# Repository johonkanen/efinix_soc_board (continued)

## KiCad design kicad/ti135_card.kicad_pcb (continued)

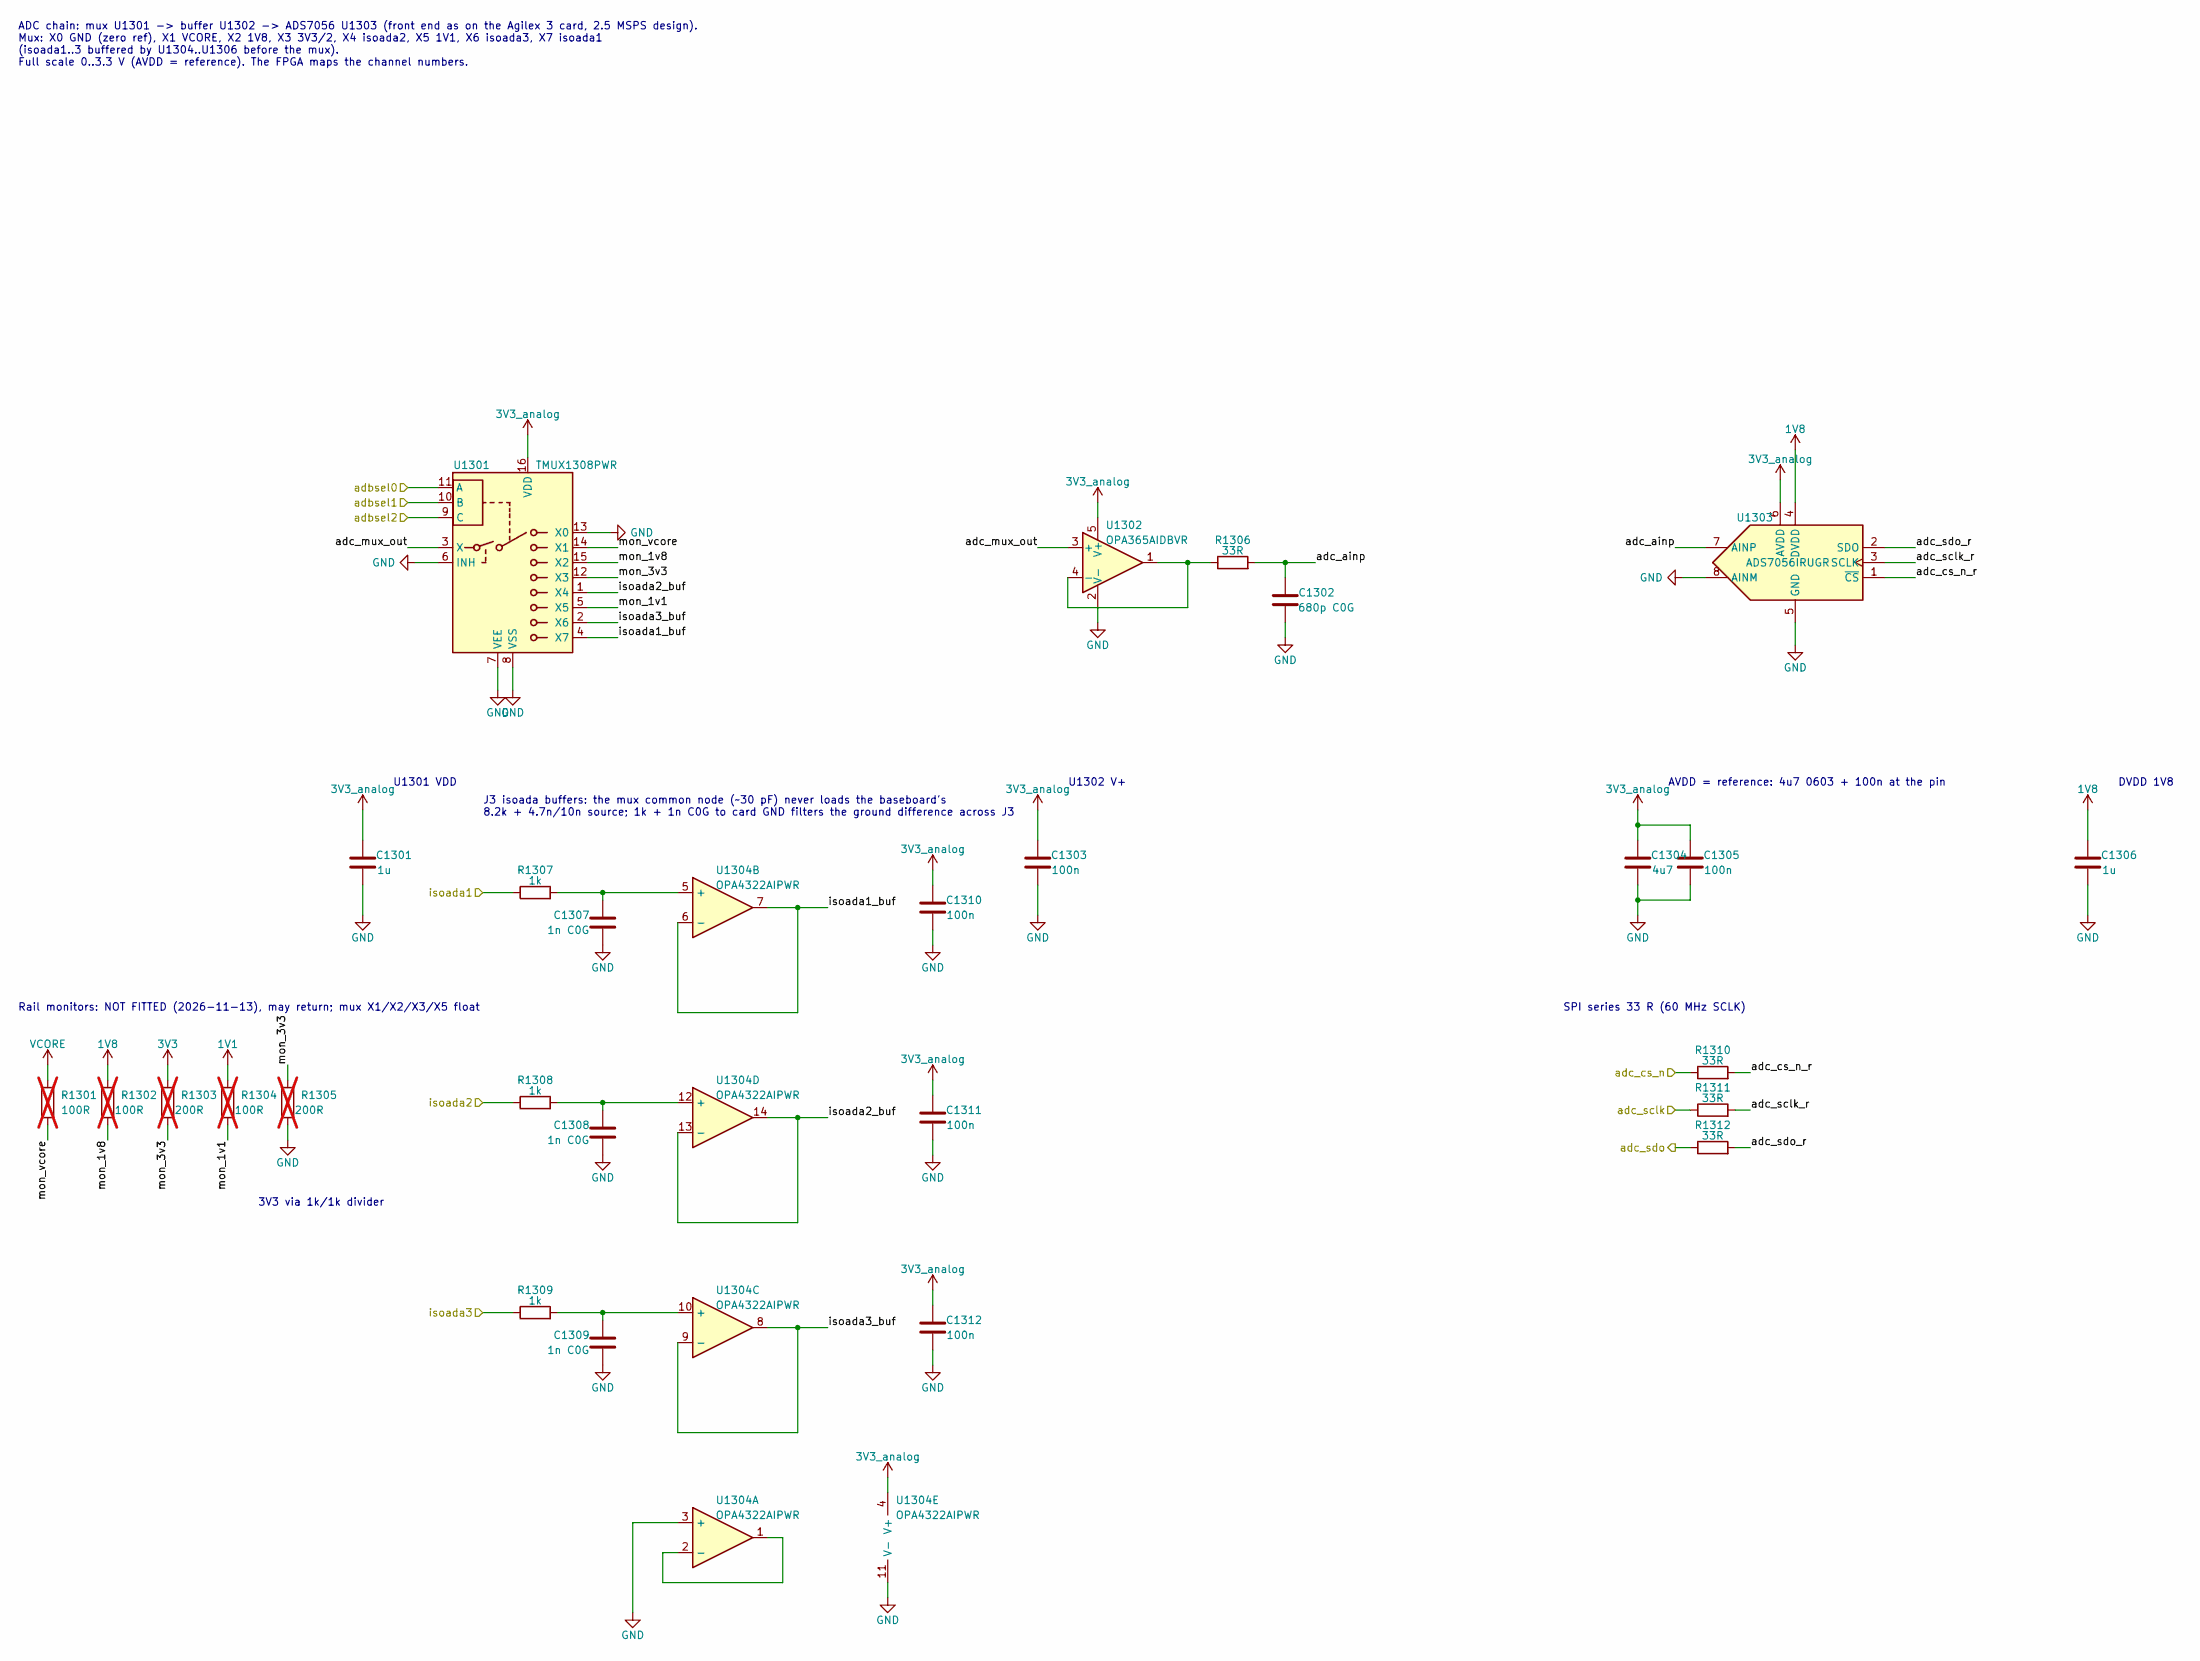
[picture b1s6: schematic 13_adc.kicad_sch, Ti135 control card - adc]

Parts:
C1301: 1u; C_0402_1005Metric; LCSC C52923
C1302: 680p C0G; C_0402_1005Metric; LCSC C126514
C1303, C1305, C1310, C1311, C1312: 100n; C_0402_1005Metric; LCSC C1525
C1304: 4u7; C_0603_1608Metric; LCSC C19666
C1306: 1u; C_0201_0603Metric; LCSC C272877
C1307, C1308, C1309: 1n C0G; C_0402_1005Metric; LCSC C76947
R1301, R1302, R1304: 100R; R_0402_1005Metric; LCSC C25076; not fitted
R1303, R1305: 200R; R_0402_1005Metric; LCSC C25087; not fitted
R1306, R1310, R1311, R1312: 33R; R_0402_1005Metric; LCSC C25105
R1307, R1308, R1309: 1k; R_0402_1005Metric; LCSC C11702
U1301: TMUX1308PWR; TSSOP-16_4.4x5mm_P0.65mm; LCSC C970231
U1302: OPA365AIDBVR; SOT-23-5; LCSC C96626
U1303: ADS7056IRUGR; ads7056; LCSC C2669798
U1304: OPA4322AIPWR; TSSOP-14_4.4x5mm_P0.65mm; LCSC C486027

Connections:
1V8: C1306.1, R1302.1, U1303.4 (DVDD); also elsewhere on the board
3V3_analog: C1301.1, C1303.1, C1304.1, C1305.1, C1310.1, C1311.1, C1312.1, U1301.16 (VDD), U1302.5 (V+), U1303.6 (AVDD), U1304.4 (V+); also elsewhere on the board
/13 adc/adc_ainp: C1302.1, R1306.2, U1303.7 (AINP)
/13 adc/adc_cs_n_r: R1310.2, U1303.1 (~CS)
/13 adc/adc_mux_out: U1301.3 (X), U1302.3 (+)
/13 adc/adc_sclk_r: R1311.2, U1303.3 (SCLK)
/13 adc/adc_sdo_r: R1312.2, U1303.2 (SDO)
/13 adc/isoada1_buf: U1301.4 (X7), U1304.6 (-), U1304.7
/13 adc/isoada2_buf: U1301.1 (X4), U1304.13 (-), U1304.14
/13 adc/isoada3_buf: U1301.2 (X6), U1304.8, U1304.9 (-)
/13 adc/mon_1v1: R1304.2, U1301.5 (X5)
/13 adc/mon_1v8: R1302.2, U1301.15 (X2)
/13 adc/mon_3v3: R1303.2, R1305.1, U1301.12 (X3)
/13 adc/mon_vcore: R1301.2, U1301.14 (X1)
/adbsel0: U1301.11 (A); also elsewhere on the board
/adbsel1: U1301.10 (B); also elsewhere on the board
/adbsel2: U1301.9 (C); also elsewhere on the board
/adc_cs_n: R1310.1; also elsewhere on the board
/adc_sclk: R1311.1; also elsewhere on the board
/adc_sdo: R1312.1; also elsewhere on the board
/isoada1: R1307.1; also elsewhere on the board
/isoada2: R1308.1; also elsewhere on the board
/isoada3: R1309.1; also elsewhere on the board
GND: C1301.2, C1302.2, C1303.2, C1304.2, C1305.2, C1306.2, C1307.2, C1308.2, C1309.2, C1310.2, C1311.2, C1312.2, R1305.2, U1301.6 (INH), U1301.7 (VEE), U1301.8 (VSS), U1301.13 (X0), U1302.2 (V-), U1303.5 (GND), U1303.8 (AINM), U1304.3 (+), U1304.11 (V-); also elsewhere on the board
unnamed: R1306.1, U1302.1, U1302.4 (-)
unnamed: U1304.1, U1304.2 (-)
unnamed: C1307.1, R1307.2, U1304.5 (+)
unnamed: C1309.1, R1309.2, U1304.10 (+)
unnamed: C1308.1, R1308.2, U1304.12 (+)

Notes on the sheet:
Rail monitors: NOT FITTED (2026-11-13), may return; mux X1/X2/X3/X5 float
U1301 VDD
DVDD 1V8
SPI series 33 R (60 MHz SCLK)
U1302 V+
3V3 via 1k/1k divider
ADC chain: mux U1301 -> buffer U1302 -> ADS7056 U1303 (front end as on the Agilex 3 card, 2.5 MSPS design). Mux: X0 GND (zero ref), X1 VCORE, X2 1V8, X3 3V3/2, X4 isoada2, X5 1V1, X6 isoada3, X7 isoada1 (isoada1..3 buffered by U1304..U1306 before the mux). Full scale 0..3.3 V (AVDD = reference). Th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
J3 isoada buffers: the mux common node (~30 pF) never loads the baseboard's 8.2k + 4.7n/10n source; 1k + 1n C0G to card GND filters the ground difference across J3
AVDD = reference: 4u7 0603 + 100n at the pin

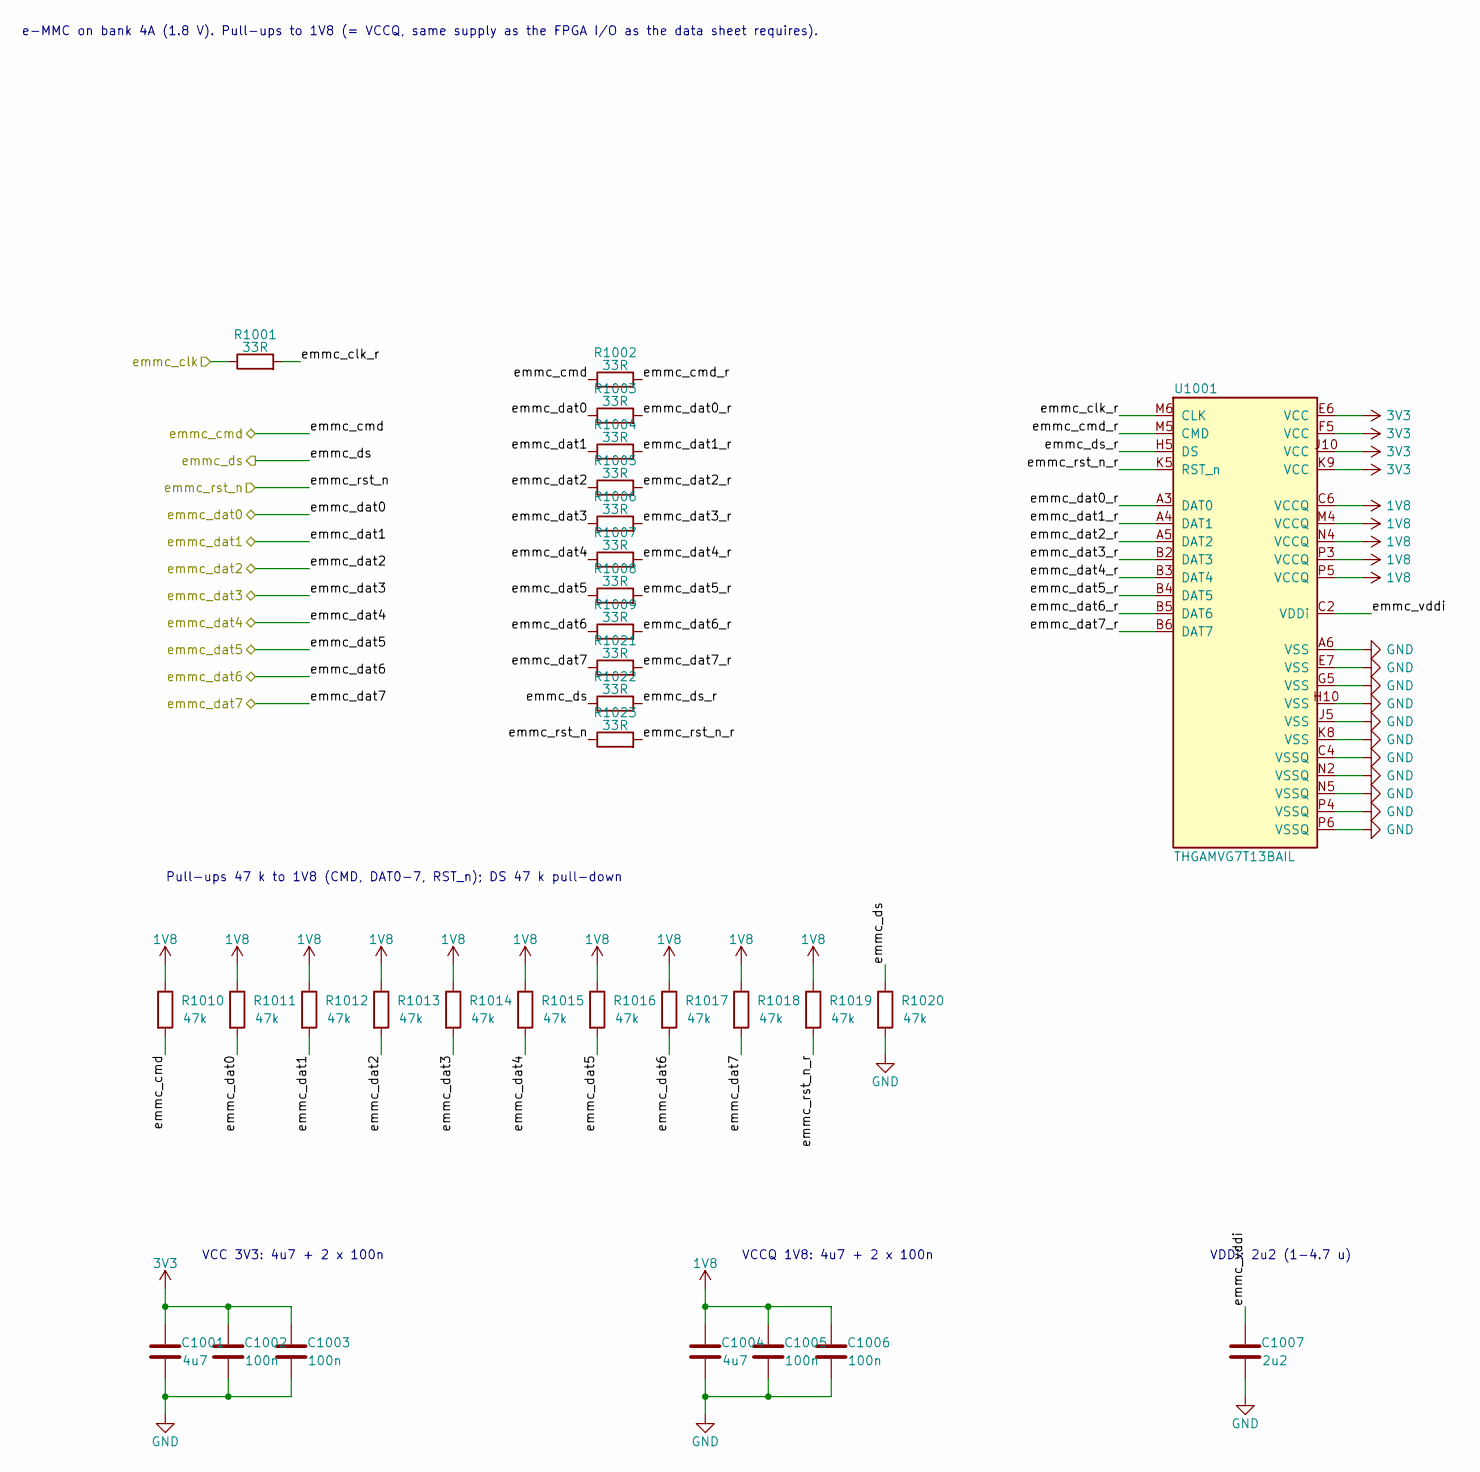
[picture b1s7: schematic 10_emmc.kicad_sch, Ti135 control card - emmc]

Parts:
C1001, C1004: 4u7; C_0201_0603Metric; LCSC C5969171
C1002, C1003, C1005, C1006: 100n; C_0201_0603Metric; LCSC C190183
C1007: 2u2; C_0201_0603Metric; LCSC C77762
R1001, R1002, R1003, R1004, R1005, R1006, R1007, R1008, R1009, R1021, R1022, R1023: 33R; R_0201_0603Metric; LCSC C320843
R1010, R1011, R1012, R1013, R1014, R1015, R1016, R1017, R1018, R1019, R1020: 47k; R_0201_0603Metric; LCSC C270345
U1001: THGAMVG7T13BAIL; LFBGA-153_11.5x13mm_Layout14x14_P0.5mm; LCSC C7599693

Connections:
1V8: C1004.1, C1005.1, C1006.1, R1010.1, R1011.1, R1012.1, R1013.1, R1014.1, R1015.1, R1016.1, R1017.1, R1018.1, R1019.1, U1001.C6 (VCCQ), U1001.M4 (VCCQ), U1001.N4 (VCCQ), U1001.P3 (VCCQ), U1001.P5 (VCCQ); also elsewhere on the board
3V3: C1001.1, C1002.1, C1003.1, U1001.E6 (VCC), U1001.F5 (VCC), U1001.J10 (VCC), U1001.K9 (VCC); also elsewhere on the board
/10 emmc/emmc_clk_r: R1001.2, U1001.M6 (CLK)
/10 emmc/emmc_cmd_r: R1002.2, U1001.M5 (CMD)
/10 emmc/emmc_dat0_r: R1003.2, U1001.A3 (DAT0)
/10 emmc/emmc_dat1_r: R1004.2, U1001.A4 (DAT1)
/10 emmc/emmc_dat2_r: R1005.2, U1001.A5 (DAT2)
/10 emmc/emmc_dat3_r: R1006.2, U1001.B2 (DAT3)
/10 emmc/emmc_dat4_r: R1007.2, U1001.B3 (DAT4)
/10 emmc/emmc_dat5_r: R1008.2, U1001.B4 (DAT5)
/10 emmc/emmc_dat6_r: R1009.2, U1001.B5 (DAT6)
/10 emmc/emmc_dat7_r: R1021.2, U1001.B6 (DAT7)
/10 emmc/emmc_ds_r: R1022.2, U1001.H5 (DS)
/10 emmc/emmc_rst_n_r: R1019.2, R1023.2, U1001.K5 (RST_n)
/10 emmc/emmc_vddi: C1007.1, U1001.C2 (VDDi)
/emmc_clk: R1001.1; also elsewhere on the board
/emmc_cmd: R1002.1, R1010.2; also elsewhere on the board
/emmc_dat0: R1003.1, R1011.2; also elsewhere on the board
/emmc_dat1: R1004.1, R1012.2; also elsewhere on the board
/emmc_dat2: R1005.1, R1013.2; also elsewhere on the board
/emmc_dat3: R1006.1, R1014.2; also elsewhere on the board
/emmc_dat4: R1007.1, R1015.2; also elsewhere on the board
/emmc_dat5: R1008.1, R1016.2; also elsewhere on the board
/emmc_dat6: R1009.1, R1017.2; also elsewhere on the board
/emmc_dat7: R1018.2, R1021.1; also elsewhere on the board
/emmc_ds: R1020.1, R1022.1; also elsewhere on the board
/emmc_rst_n: R1023.1; also elsewhere on the board
GND: C1001.2, C1002.2, C1003.2, C1004.2, C1005.2, C1006.2, C1007.2, R1020.2, U1001.A6 (VSS), U1001.C4 (VSSQ), U1001.E7 (VSS), U1001.G5 (VSS), U1001.H10 (VSS), U1001.J5 (VSS), U1001.K8 (VSS), U1001.N2 (VSSQ), U1001.N5 (VSSQ), U1001.P4 (VSSQ), U1001.P6 (VSSQ); also elsewhere on the board

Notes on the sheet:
VCCQ 1V8: 4u7 + 2 x 100n
Pull-ups 47 k to 1V8 (CMD, DAT0-7, RST_n); DS 47 k pull-down
VCC 3V3: 4u7 + 2 x 100n
e-MMC on bank 4A (1.8 V). Pull-ups to 1V8 (= VCCQ, same supply as the FPGA I/O as the data sheet requires).
VDDi: 2u2 (1-4.7 u)

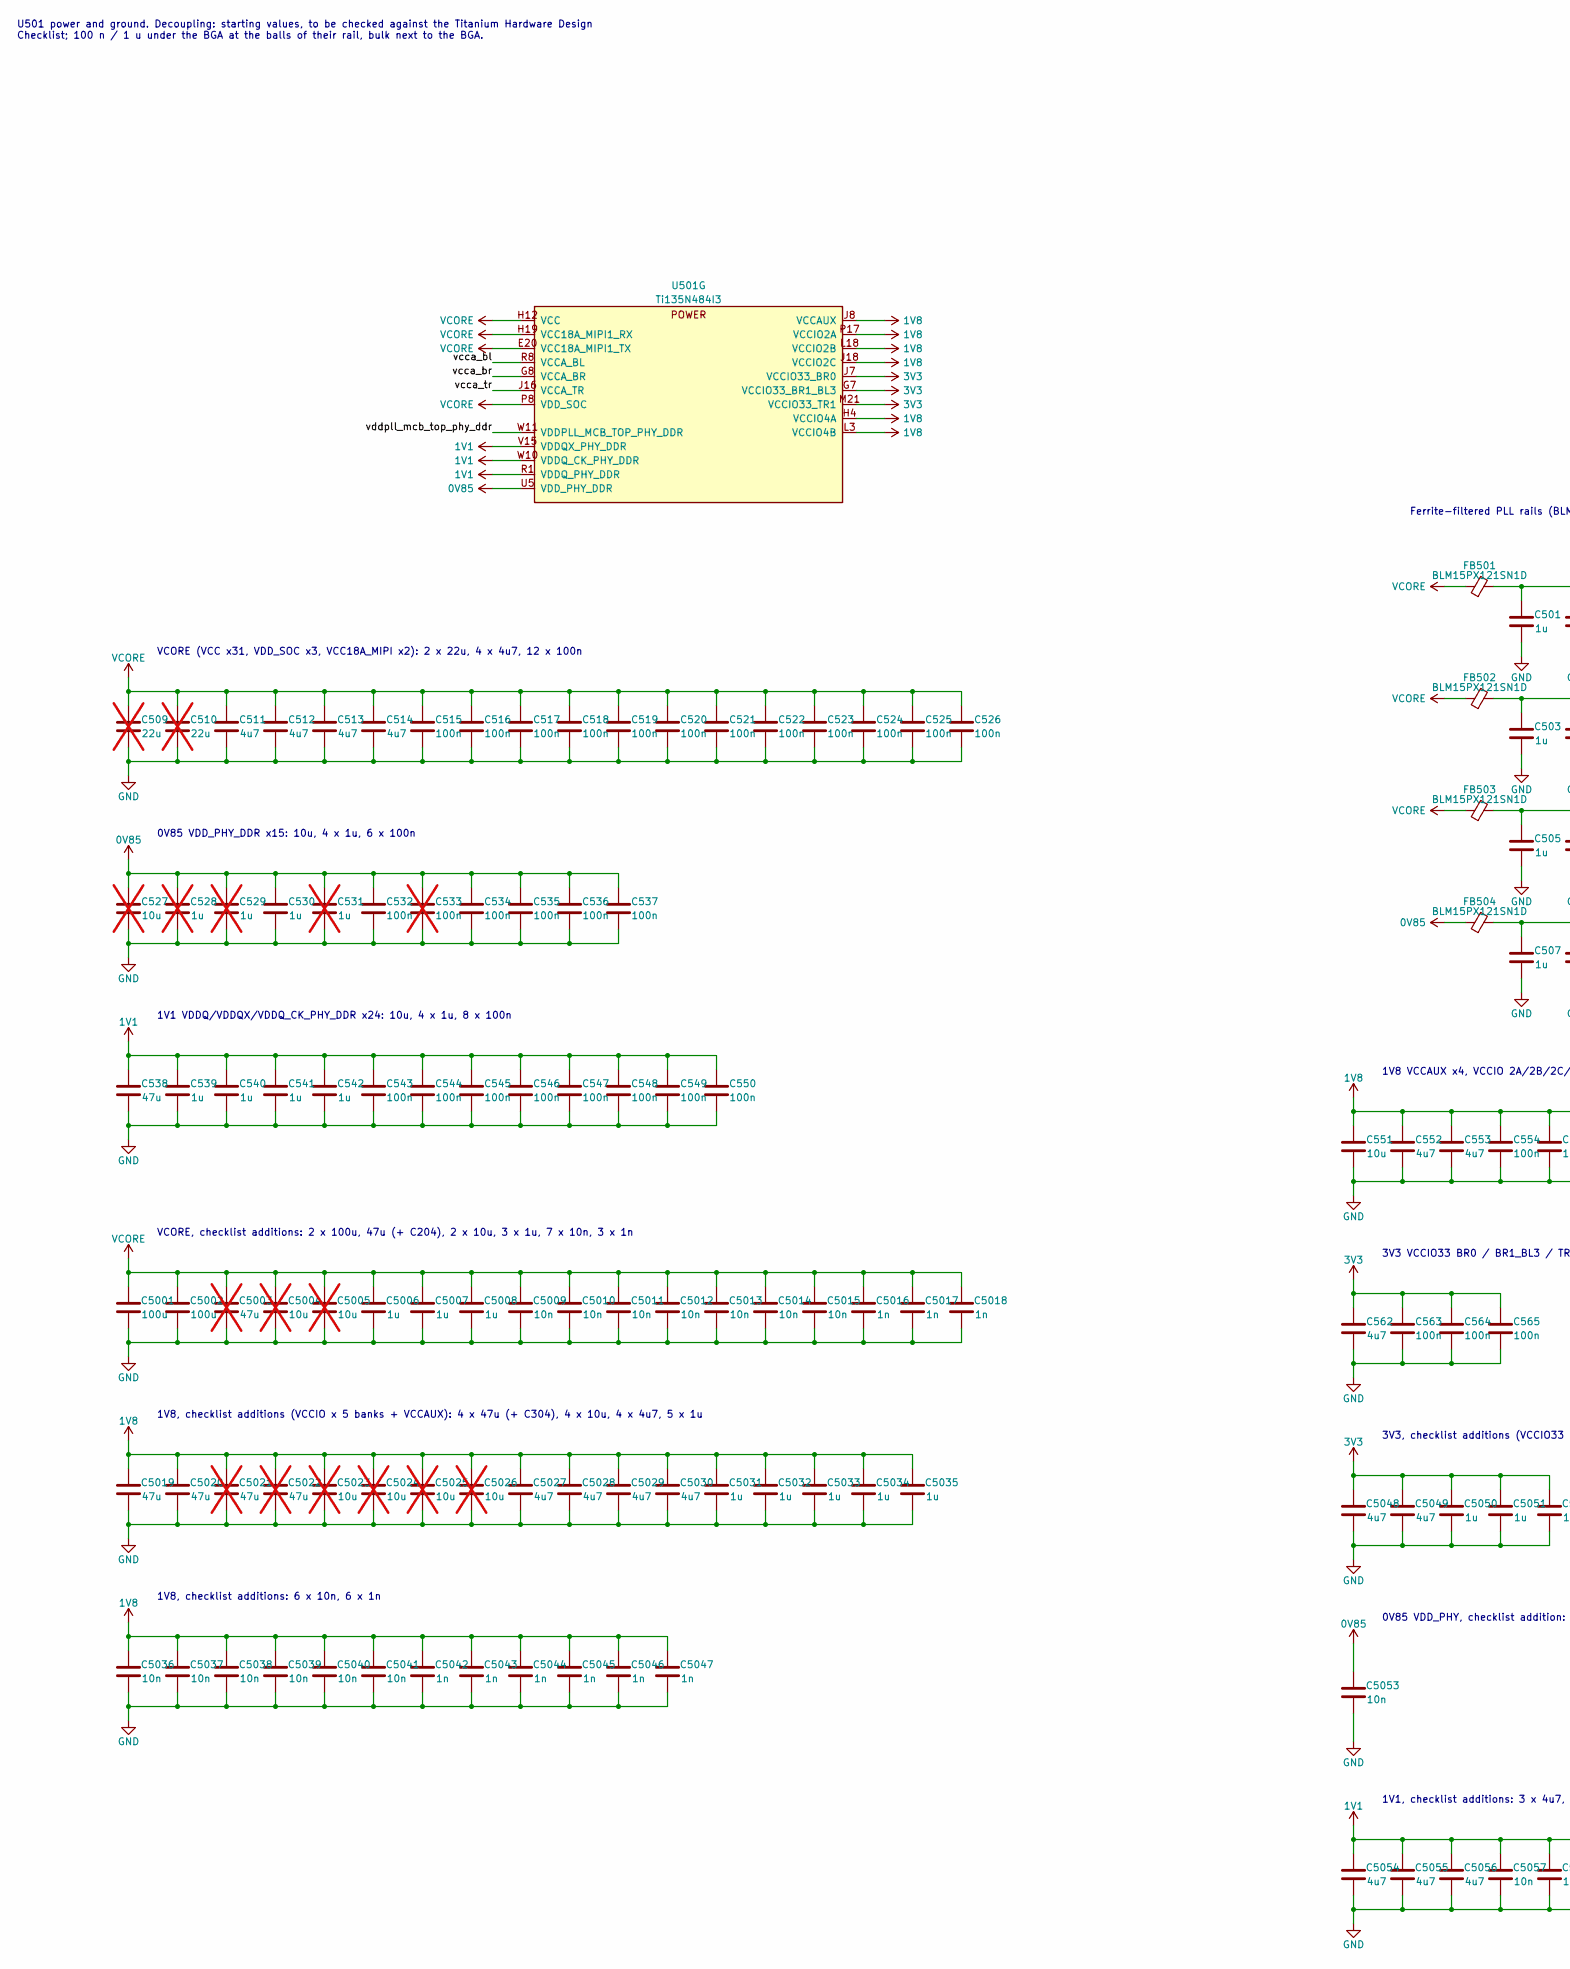
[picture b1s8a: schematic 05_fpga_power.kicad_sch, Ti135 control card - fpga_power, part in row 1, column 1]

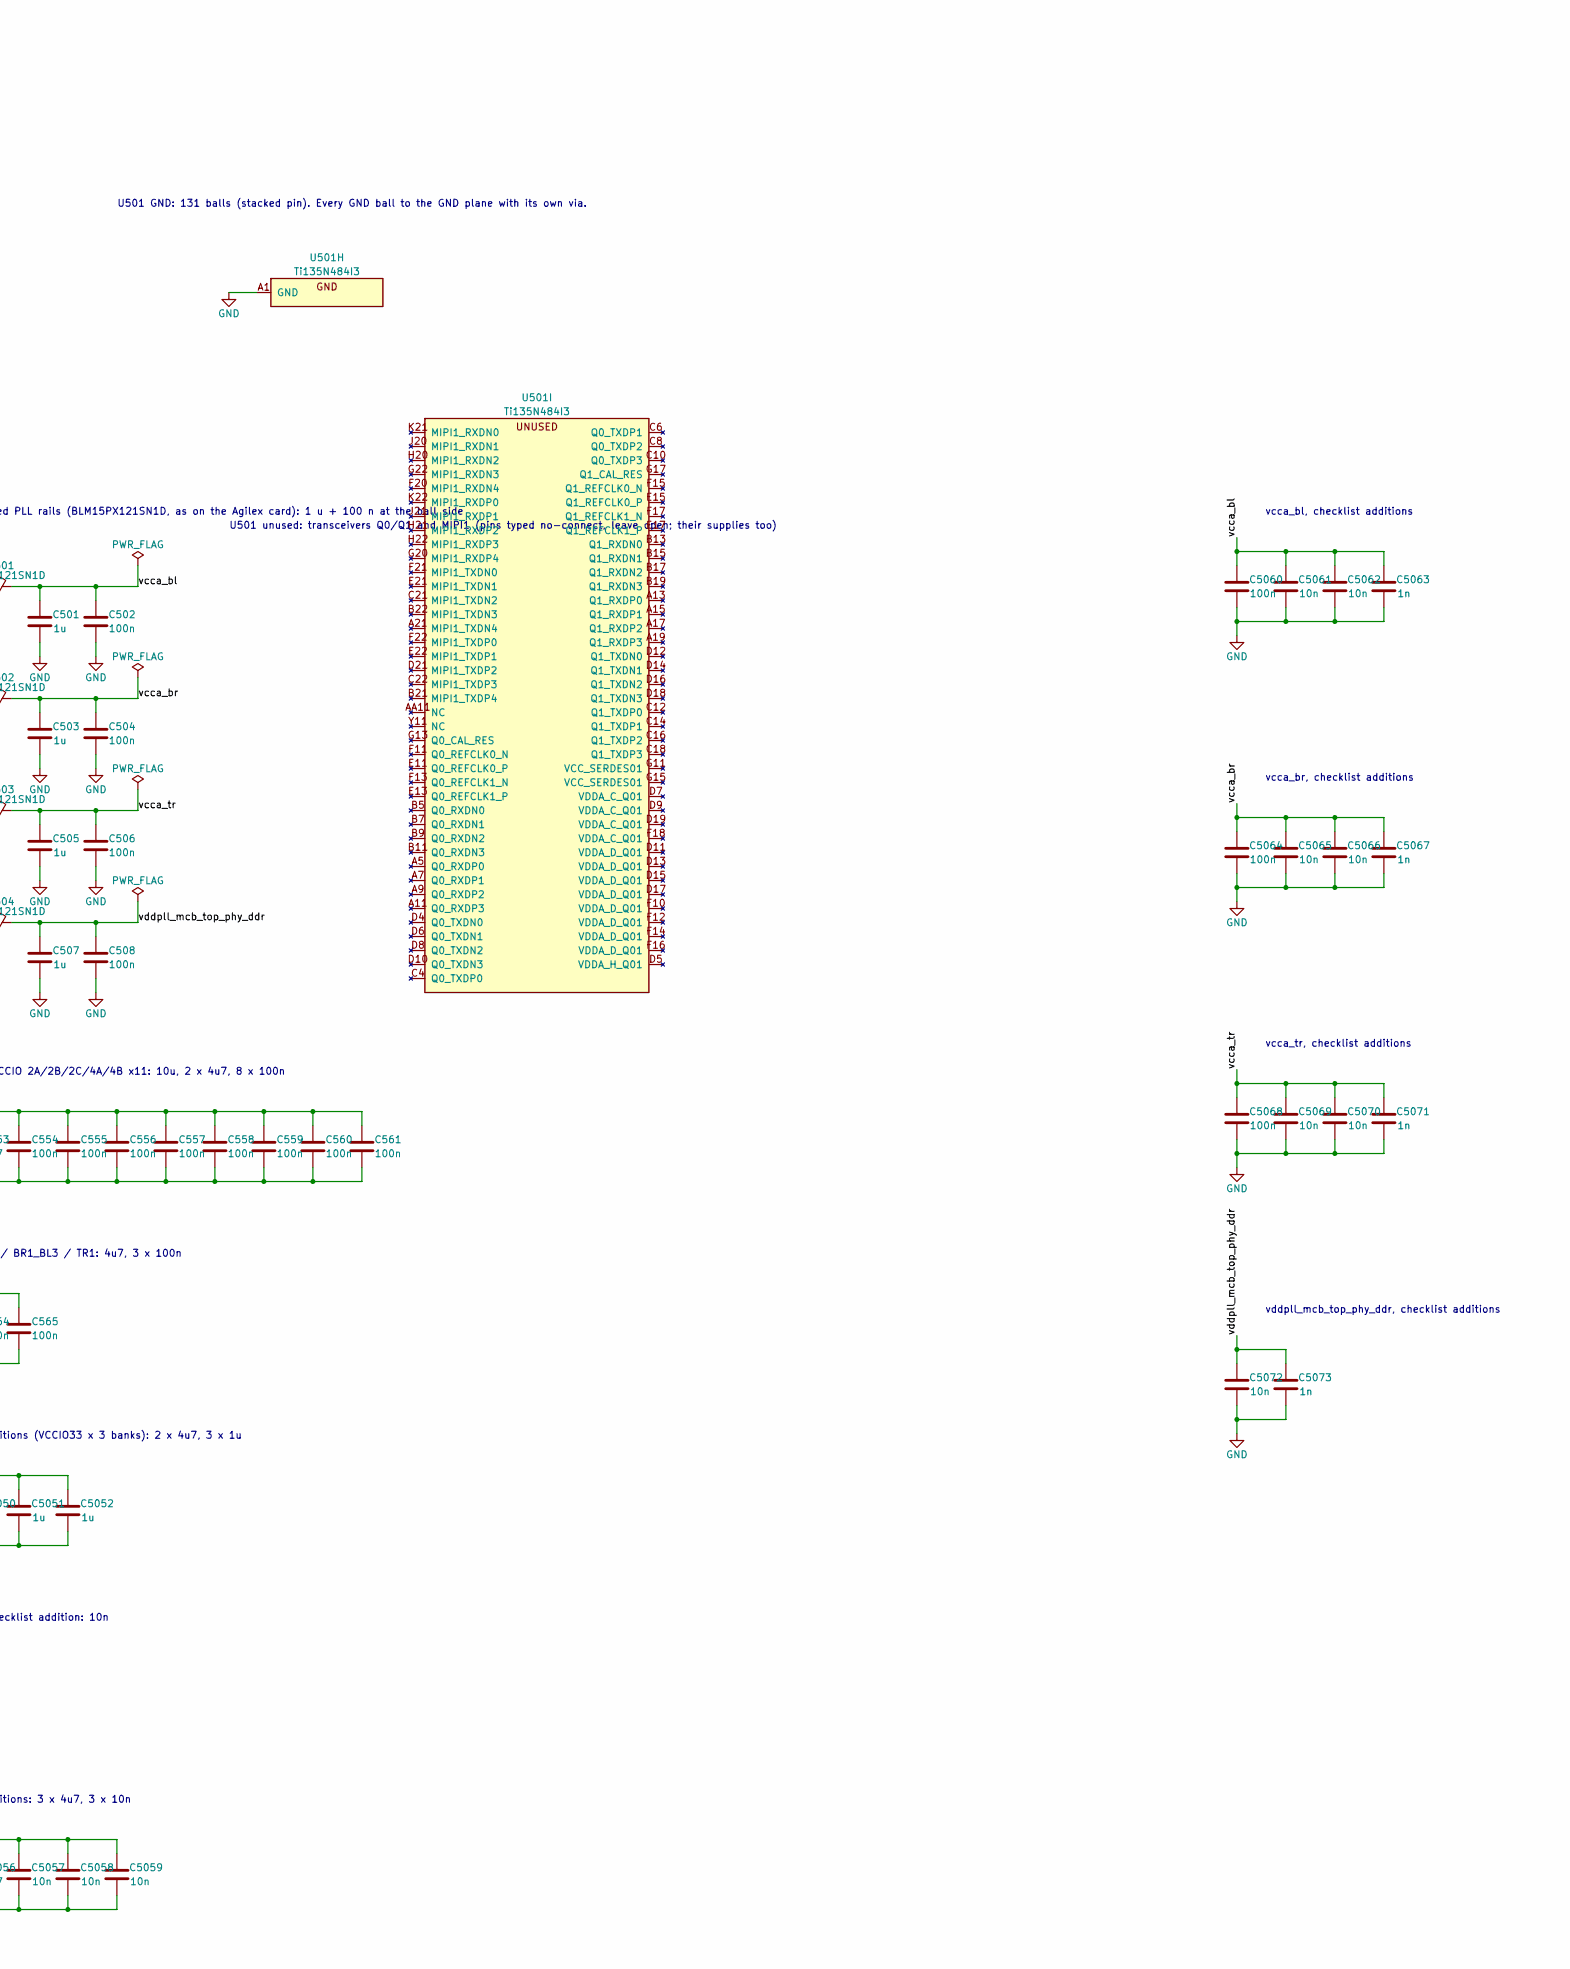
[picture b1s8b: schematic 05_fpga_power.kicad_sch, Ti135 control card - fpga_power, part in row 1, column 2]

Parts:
C501, C503, C505, C507, C5033: 1u; C_0402_1005Metric; LCSC C52923
C502, C504, C506, C508: 100n; C_0402_1005Metric; LCSC C1525
C509, C510: 22u; C_0805_2012Metric; LCSC C45783; not fitted
C511, C512, C513, C514, C552, C553, C5027, C5028, C5029, C5030, C5048, C5049, C5054, C5055, C5056: 4u7; C_0201_0603Metric; LCSC C47117441
C515, C516, C517, C518, C519, C520, C521, C522, C523, C524, C525, C526, C532, C534, C535, C536, C537, C543, C544, C545, C546, C547, C548, C549, C550, C554, C555, C556, C557, C558, C559, C560, C561, C563, C564, C565, C5060, C5064, C5068: 100n; C_0201_0603Metric; LCSC C190183
C527, C5004, C5005, C5023, C5024, C5025, C5026: 10u; C_0805_2012Metric; LCSC C15850; not fitted
C528, C529, C531: 1u; C_0201_0603Metric; LCSC C272877; not fitted
C530, C539, C540, C541, C542, C5006, C5007, C5008, C5031, C5032, C5034, C5035, C5050, C5051, C5052: 1u; C_0201_0603Metric; LCSC C272877
C533: 100n; C_0201_0603Metric; LCSC C190183; not fitted
C538, C5019, C5020: 47u; C_0805_2012Metric; LCSC C16780
C551: 10u; C_0805_2012Metric; LCSC C15850
C562: 4u7; C_0402_1005Metric; LCSC C23733
C5001, C5002: 100u; C_1206_3216Metric; LCSC C15008
C5003, C5021, C5022: 47u; C_0805_2012Metric; LCSC C16780; not fitted
C5009, C5010, C5011, C5012, C5013, C5014, C5015, C5036, C5037, C5038, C5039, C5040, C5041, C5053, C5057, C5058, C5059, C5061, C5062, C5065, C5066, C5069, C5070, C5072: 10n; C_0201_0603Metric; LCSC C76941
C5016, C5017, C5018, C5042, C5043, C5044, C5045, C5046, C5047, C5063, C5067, C5071, C5073: 1n; C_0201_0603Metric; LCSC C66942
FB501, FB502, FB503, FB504: BLM15PX121SN1D; L_0402_1005Metric; LCSC C88970
U501: Ti135N484I3; LFBGA-484_18x18mm_Layout22x22_P0.8mm

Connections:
0V85: C527.1, C528.1, C529.1, C530.1, C531.1, C532.1, C533.1, C534.1, C535.1, C536.1, C537.1, C5053.1, FB504.1, U501.U5 (VDD_PHY_DDR), U501.U6 (VDD_PHY_DDR), U501.U7 (VDD_PHY_DDR), U501.U8 (VDD_PHY_DDR), U501.U9 (VDD_PHY_DDR), U501.U10 (VDD_PHY_DDR), U501.U11 (VDD_PHY_DDR), U501.U12 (VDD_PHY_DDR), U501.U13 (VDD_PHY_DDR), U501.U14 (VDD_PHY_DDR), U501.U15 (VDD_PHY_DDR), U501.V7 (VDD_PHY_DDR), U501.V9 (VDD_PHY_DDR), U501.V11 (VDD_PHY_DDR), U501.V13 (VDD_PHY_DDR); also elsewhere on the board
1V1: C538.1, C539.1, C540.1, C541.1, C542.1, C543.1, C544.1, C545.1, C546.1, C547.1, C548.1, C549.1, C550.1, C5054.1, C5055.1, C5056.1, C5057.1, C5058.1, C5059.1, U501.AB3 (VDDQ_PHY_DDR), U501.R1 (VDDQ_PHY_DDR), U501.T2 (VDDQ_PHY_DDR), U501.T5 (VDDQ_PHY_DDR), U501.U18 (VDDQ_PHY_DDR), U501.U19 (VDDQ_PHY_DDR), U501.V1 (VDDQ_PHY_DDR), U501.V15 (VDDQX_PHY_DDR), U501.V20 (VDDQ_PHY_DDR), U501.V21 (VDDQ_PHY_DDR), U501.W6 (VDDQX_PHY_DDR), U501.W7 (VDDQX_PHY_DDR), U501.W8 (VDDQX_PHY_DDR), U501.W9 (VDDQX_PHY_DDR), U501.W10 (VDDQ_CK_PHY_DDR), U501.W12 (VDDQX_PHY_DDR), U501.W15 (VDDQX_PHY_DDR), U501.W17 (VDDQ_PHY_DDR), U501.Y3 (VDDQ_PHY_DDR), U501.Y6 (VDDQ_PHY_DDR), U501.Y8 (VDDQ_PHY_DDR), U501.Y10 (VDDQX_PHY_DDR), U501.Y12 (VDDQ_PHY_DDR), U501.Y22 (VDDQ_PHY_DDR); also elsewhere on the board
1V8: C551.1, C552.1, C553.1, C554.1, C555.1, C556.1, C557.1, C558.1, C559.1, C560.1, C561.1, C5019.1, C5020.1, C5021.1, C5022.1, C5023.1, C5024.1, C5025.1, C5026.1, C5027.1, C5028.1, C5029.1, C5030.1, C5031.1, C5032.1, C5033.1, C5034.1, C5035.1, C5036.1, C5037.1, C5038.1, C5039.1, C5040.1, C5041.1, C5042.1, C5043.1, C5044.1, C5045.1, C5046.1, C5047.1, U501.H4 (VCCIO4A), U501.J8 (VCCAUX), U501.J18 (VCCIO2C), U501.K5 (VCCIO4A), U501.L3 (VCCIO4B), U501.L18 (VCCIO2B), U501.M6 (VCCIO4A), U501.M16 (VCCAUX), U501.N4 (VCCIO4B), U501.N8 (VCCAUX), U501.N19 (VCCIO2B), U501.P2 (VCCIO4B), U501.P17 (VCCIO2A), U501.T4 (VCCIO4B), U501.U16 (VCCAUX); also elsewhere on the board
3V3: C562.1, C563.1, C564.1, C565.1, C5048.1, C5049.1, C5050.1, C5051.1, C5052.1, U501.G7 (VCCIO33_BR1_BL3), U501.J7 (VCCIO33_BR0), U501.M21 (VCCIO33_TR1); also elsewhere on the board
/05 fpga_power/vcca_bl: C501.1, C502.1, C5060.1, C5061.1, C5062.1, C5063.1, FB501.2, U501.R8 (VCCA_BL)
/05 fpga_power/vcca_br: C503.1, C504.1, C5064.1, C5065.1, C5066.1, C5067.1, FB502.2, U501.G8 (VCCA_BR)
/05 fpga_power/vcca_tr: C505.1, C506.1, C5068.1, C5069.1, C5070.1, C5071.1, FB503.2, U501.J16 (VCCA_TR)
/05 fpga_power/vddpll_mcb_top_phy_ddr: C507.1, C508.1, C5072.1, C5073.1, FB504.2, U501.W11 (VDDPLL_MCB_TOP_PHY_DDR)
GND: C501.2, C502.2, C503.2, C504.2, C505.2, C506.2, C507.2, C508.2, C509.2, C510.2, C511.2, C512.2, C513.2, C514.2, C515.2, C516.2, C517.2, C518.2, C519.2, C520.2, C521.2, C522.2, C523.2, C524.2, C525.2, C526.2, C527.2, C528.2, C529.2, C530.2, C531.2, C532.2, C533.2, C534.2, C535.2, C536.2, C537.2, C538.2, C539.2, C540.2, C541.2, C542.2, C543.2, C544.2, C545.2, C546.2, C547.2, C548.2, C549.2, C550.2, C551.2, C552.2, C553.2, C554.2, C555.2, C556.2, C557.2, C558.2, C559.2, C560.2, C561.2, C562.2, C563.2, C564.2, C565.2, C5001.2, C5002.2, C5003.2, C5004.2, C5005.2, C5006.2, C5007.2, C5008.2, C5009.2, C5010.2, C5011.2, C5012.2, C5013.2, C5014.2, C5015.2, C5016.2, C5017.2, C5018.2, C5019.2, C5020.2, C5021.2, C5022.2, C5023.2, C5024.2, C5025.2, C5026.2, C5027.2, C5028.2, C5029.2, C5030.2, C5031.2, C5032.2, C5033.2, C5034.2, C5035.2, C5036.2, C5037.2, C5038.2, C5039.2, C5040.2, C5041.2, C5042.2, C5043.2, C5044.2, C5045.2, C5046.2, C5047.2, C5048.2, C5049.2, C5050.2, C5051.2, C5052.2, C5053.2, C5054.2, C5055.2, C5056.2, C5057.2, C5058.2, C5059.2, C5060.2, C5061.2, C5062.2, C5063.2, C5064.2, C5065.2, C5066.2, C5067.2, C5068.2, C5069.2, C5070.2, C5071.2, C5072.2, C5073.2, U501.A1 (GND), U501.A4 (GND), U501.A6 (GND), U501.A8 (GND), U501.A10 (GND), U501.A12 (GND), U501.A14 (GND), U501.A16 (GND), U501.A18 (GND), U501.A20 (GND), U501.A22 (GND), U501.AB1 (GND), U501.AB4 (GND), U501.AB6 (GND), U501.AB8 (GND), U501.AB10 (GND), U501.AB12 (GND), U501.AB14 (GND), U501.AB16 (GND), U501.AB18 (GND), U501.AB20 (GND), U501.AB22 (GND), U501.B3 (GND), U501.B4 (GND), U501.B6 (GND), U501.B8 (GND), U501.B10 (GND), U501.B12 (GND), U501.B14 (GND), U501.B16 (GND), U501.B18 (GND), U501.B20 (GND), U501.C3 (GND), U501.C5 (GND), U501.C7 (GND), U501.C9 (GND), U501.C11 (GND), U501.C13 (GND), U501.C15 (GND), U501.C17 (GND), U501.C19 (GND), U501.C20 (GND), U501.D1 (GND), U501.D3 (GND), U501.D20 (GND), U501.D22 (GND), U501.E3 (GND), U501.E4 (GND), U501.E5 (GND), U501.E6 (GND), U501.E7 (GND), U501.E8 (GND), U501.E9 (GND), U501.E10 (GND), U501.E12 (GND), U501.E14 (GND), U501.E16 (GND), U501.E18 (GND), U501.E19 (GND), U501.F19 (GND), U501.G1 (GND), U501.G12 (GND), U501.G14 (GND), U501.G16 (GND), U501.G18 (GND), U501.G19 (GND), U501.G21 (GND), U501.H13 (GND), U501.H15 (GND), U501.H17 (GND), U501.H18 (GND), U501.J2 (GND), U501.J10 (GND), U501.J12 (GND), U501.J14 (GND), U501.J22 (GND), U501.K8 (GND), U501.K9 (GND), U501.K11 (GND), U501.K13 (GND), U501.K15 (GND), U501.K20 (GND), U501.L10 (GND), U501.L12 (GND), U501.L14 (GND), U501.M1 (GND), U501.M9 (GND), U501.M11 (GND), U501.M13 (GND), U501.M15 (GND), U501.N10 (GND), U501.N12 (GND), U501.N14 (GND), U501.P7 (GND), U501.P9 (GND), U501.P11 (GND), U501.P13 (GND), U501.P15 (GND), U501.P22 (GND), U501.R5 (GND), U501.R10 (GND), U501.R12 (GND), U501.R14 (GND), U501.R20 (GND), U501.T1 (GND), U501.T3 (GND), U501.T7 (GND), U501.T9 (GND), U501.T11 (GND), U501.T13 (GND), U501.T15 (GND), U501.T18 (GND), U501.U17 (GND), U501.U21 (GND), U501.V2 (GND), U501.V4 (GND), U501.V6 (GND), U501.V8 (GND), U501.V10 (GND), U501.V12 (GND), U501.V14 (GND), U501.V19 (GND), U501.V22 (GND), U501.Y1 (GND), U501.Y5 (GND), U501.Y7 (GND), U501.Y13 (GND), U501.Y15 (GND), U501.Y17 (GND), U501.Y19 (GND), U501.Y21 (GND); also elsewhere on the board
VCORE: C509.1, C510.1, C511.1, C512.1, C513.1, C514.1, C515.1, C516.1, C517.1, C518.1, C519.1, C520.1, C521.1, C522.1, C523.1, C524.1, C525.1, C526.1, C5001.1, C5002.1, C5003.1, C5004.1, C5005.1, C5006.1, C5007.1, C5008.1, C5009.1, C5010.1, C5011.1, C5012.1, C5013.1, C5014.1, C5015.1, C5016.1, C5017.1, C5018.1, FB501.1, FB502.1, FB503.1, U501.E20 (VCC18A_MIPI1_TX), U501.H12 (VCC), U501.H14 (VCC), U501.H16 (VCC), U501.H19 (VCC18A_MIPI1_RX), U501.J9 (VCC), U501.J11 (VCC), U501.J13 (VCC), U501.J15 (VCC), U501.K10 (VCC), U501.K12 (VCC), U501.K14 (VCC), U501.L9 (VCC), U501.L11 (VCC), U501.L13 (VCC), U501.L15 (VCC), U501.M10 (VCC), U501.M12 (VCC), U501.M14 (VCC), U501.N9 (VCC), U501.N11 (VCC), U501.N13 (VCC), U501.N15 (VCC), U501.P8 (VDD_SOC), U501.P10 (VCC), U501.P12 (VCC), U501.P14 (VCC), U501.R7 (VDD_SOC), U501.R9 (VCC), U501.R11 (VCC), U501.R13 (VCC), U501.R15 (VCC), U501.T8 (VDD_SOC), U501.T10 (VCC), U501.T12 (VCC), U501.T14 (VCC); also elsewhere on the board

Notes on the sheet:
VCORE, checklist additions: 2 x 100u, 47u (+ C204), 2 x 10u, 3 x 1u, 7 x 10n, 3 x 1n
VCORE (VCC x31, VDD_SOC x3, VCC18A_MIPI x2): 2 x 22u, 4 x 4u7, 12 x 100n
0V85 VDD_PHY_DDR x15: 10u, 4 x 1u, 6 x 100n
3V3 VCCIO33 BR0 / BR1_BL3 / TR1: 4u7, 3 x 100n
1V8, checklist additions: 6 x 10n, 6 x 1n
U501 GND: 131 balls (stacked pin). Every GND ball to the GND plane with its own via.
1V8, checklist additions (VCCIO x 5 banks + VCCAUX): 4 x 47u (+ C304), 4 x 10u, 4 x 4u7, 5 x 1u
vddpll_mcb_top_phy_ddr, checklist additions
U501 power and ground. Decoupling: starting values, to be checked against the Titanium Hardware Design Checklist; 100 n / 1 u under the BGA at the balls of their rail, bulk next to the BGA.
vcca_br, checklist additions
1V8 VCCAUX x4, VCCIO 2A/2B/2C/4A/4B x11: 10u, 2 x 4u7, 8 x 100n
vcca_bl, checklist additions
U501 unused: transceivers Q0/Q1 and MIPI1 (pins typed no-connect, leave open; their supplies too)
3V3, checklist additions (VCCIO33 x 3 banks): 2 x 4u7, 3 x 1u
1V1, checklist additions: 3 x 4u7, 3 x 10n
1V1 VDDQ/VDDQX/VDDQ_CK_PHY_DDR x24: 10u, 4 x 1u, 8 x 100n
Ferrite-filtered PLL rails (BLM15PX121SN1D, as on the Agilex card): 1 u + 100 n at the ball side
0V85 VDD_PHY, checklist addition: 10n
vcca_tr, checklist additions
